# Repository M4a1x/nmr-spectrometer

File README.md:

<div align="center">
  
</div>

<div align="center">Building a 25MHz NMR spectrometer<br \>01.04.2023 - 30.09.2023</div>

<div align="center">

</div>

---

<div align="center"> magnETHical is a simple low-cost low-field 0.6T NMR spectrometer based on a RedPitaya and custom hardware. This repository contains everything to build your own. This includes simulations, specifications, full hardware descriptions and CAD designs, Python control code and reproducible measurement results.
</div>

## 📝 Table of Contents
- [📝 Table of Contents](#-table-of-contents)
- [🧐 About ](#-about-)
- [🏁 Getting Started ](#-getting-started-)
  - [✅ Prerequisites](#-prerequisites)
  - [🔧 Hardware](#-hardware)
  - [🖥️ Software](#️-software)
- [⚙️ Running the tests ](#️-running-the-tests-)
- [🧪 Usage ](#-usage-)
- [⛏️ Built Using ](#️-built-using-)
- [✍️ Authors ](#️-authors-)
- [🎉 Acknowledgements ](#-acknowledgements-)

## 🧐 About 
Since the discovery of the Zeeman effect in 1896 and its first use for spectroscopy in the 1940s a lot of technological advancements enabled the capture of increasingly better spectrums and the development of increasingly advanced techniques. Unfortunately, this advancement isn't cheap. Modern NMR spectroscopes cost a fortune, limiting access to this technology to well-funded research institutes, keeping out institutes from the southern hemisphere and limiting its exposure.

magnETHical seeks to provide a low-cost low-field NMR system not only capable of relaxometry but also spectroscopy for a price about an order of magnitude lower than existing devices. It's an open-source well-documented system that can be fully assembled in-house and consists of flexible components that are easily and readily available. 90% of the current ~10k€ price tag is comprised of the magnet with room for at least halving the price in the foreseeable future.

This repository seeks to provide everything needed to order, assemble and operate your own magnETHical NMR spectrometer.

## 🏁 Getting Started 

### ✅ Prerequisites
Great care has been taken to only use widely available free and open-source software so that this project may be built by anyone without any software licensing fees.

Throughout this README and the linked READMEs below a basic familiarity with the used software is assumed. However, anyone with some time on their hands should be able to follow them without much trouble after a very basic introduction to these programs. If you have trouble understanding any of the instructions, please feel free to open an issue - it's likely an error in this documentation and not on your side.

### 🔧 Hardware
The hardware consists of five main parts
- the [magnet](),
- the [digital signal generation, reception and processing board](),
- the [analogue amplification board](),
- the [electrical shimming system]() and
- the [NMR probe]().

Each of these parts can be built, assembled and verified independently of each other. For instructions on building these sub-systems, see the respective READMEs linked in the list above.

With all parts built, the final system needs to be assembled according to the following schematic.

The final assembly then looks something like this

### 🖥️ Software
Having built the hardware above the [Python control software]() can be used to capture spectra. See the linked article for a detailed guide on how to set up the software. We recommend a dedicated computer setup to run the experiments.

## ⚙️ Running the tests 
The simplest test is running marcos test without/with water. measure coil ringing

Explain how to run the automated tests for this system.

## 🧪 Usage 
To record spectra...

How to use the software/hardware. Recomenndations on analysis (Jupyter...)
Add notes about how to use the system.

## ⛏️ Built Using 

- Hardware
  - [KiCAD](https://www.kicad.org/) - ECAD for PCB Design
  - [FreeCAD](https://www.freecad.org/) - MCAD for Enclosures
  - [OpenSCAD](https://openscad.org/) - Parametric CAD for the probe
  - [LTSpice](https://www.analog.com/en/design-center/design-tools-and-calculators/ltspice-simulator.html) - Simulation of electronic circuits
- Software
  - [MaRCoS](https://github.com/vnegnev/marcos_extras) - Low-level control software for the RedPitaya and FPGA
  - [NumPy](https://numpy.org/)/[SciPy](https://scipy.org/)/[Matplotlib](https://matplotlib.org/) - High-level control software and analysis
- Documentation
  - [LaTeX](https://www.latex-project.org/) - Advanced typesetting system
  - [Sphinx](https://www.sphinx-doc.org) - Beautiful documentation

## ✍️ Authors 
- [Maximilian Stabel](mailto:mstabel@student.ethz.ch) - Idea & Initial work including Hardware & Software

## 🎉 Acknowledgements 
- Supervisor
  - [**Takuya Segawa**](https://chab.ethz.ch/forschung/institute-und-laboratorien/LPC/personen/people-details.html?persid=120573) for his supervision and encouragement
- Professors
  - [**Roland Riek**](https://chab.ethz.ch/en/the-department/people/faculty/person-detail.rriek.html) for giving me this opportunity
  - [**Sebastian Kozerke**](https://biomed.ee.ethz.ch/institute/People/person-detail.html?persid=61641) for taking me in as his Master's student
- Support
  - [**Alexander Däpp**](https://ssnmr.ethz.ch/the-group/people/person-detail.html?persid=147372) for his support and patience with the RF hardware
  - [**Tiago Ferreira das Neves**](https://chab.ethz.ch/en/the-department/people/a-z/person-detail.MjU3NzM4.TGlzdC82MDEsLTIxMzAxOTI4MDM=.html) for his electronics support

<div align="center">
  
</div>

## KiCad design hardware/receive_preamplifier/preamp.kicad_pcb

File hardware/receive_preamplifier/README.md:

# RX LNA Preamp

This folder contains the first amplifier in the RX chain, based on the [design of Martinos RF Lab](https://rflab.martinos.org/index.php?title=Low-noise_RF_Preamplifier) with the [PHA-13LN+](https://www.minicircuits.com/pdfs/PHA-13LN+.pdf) chip from mini-circuits.

This design could easily be adapted to be included in an all-in-one board including an RX preamplifier, RX amplifier, TX amplifier, TX power amplifier and TX/RX switch.

The design was adapted using the newest KiCAD version (7.0.2, 12.05.2023).

## Specifications
The receive amplifier needs to amplify the signal from uW level (~-30dbm, [Louis-Joesph and Lesot (2022)](../../literature/related_projects/foss_nmr_spectrometer_15MHz.pdf)) to around -2dbm (~0.5V @ 50Ohm) for the 16-bit ADC of the RedPitaya. Thus a gain of at least 28dB is needed. Previous work (see below) uses either a two or even three-stage design.

Furthermore, the design should be simple and easily reproducible. At best, it should be hand-solderable, without the need for a reflow oven or hot air gun. The parts should be easy to obtain and a low part count would be desirable as well. The target/carrier frequency is at 25MHz corresponding to the 1H Larmor frequency of the 0.6T magnet we're using.

One option would be to use an amplifier chain similar to [Martinos (MIT) lab](https://rflab.martinos.org/index.php?title=Main_Page) used in their MRI experiments for the reception. This consists of three stages, two PHA-13LN+ (~20€/eval board ~140€) and one ZFL-500LN+ (~125€). Sometimes the RX LNAs are already integrated into the T/R Switch - e.g. the [T/R Switch from Menküc](https://github.com/menkueclab/TR-Switch) uses the two PHA-13LN+ LNAs based on the design from Martinos lab. Since the maximum output level of the PHA-13LN+ is sufficiently high three PHA-LN13+ could be used as well.
> **TODO**
> Experimentally verify that 40dB (vs the 30dB estimate) are suitable for us, or if we need more/less amplification.

## Previous Work/Inspirations
- [Martinos Lab](https://rflab.martinos.org/index.php?title=Low-noise_RF_Preamplifier) uses a 3-stage design for their low-noise RF preamplifier. It consists of two PHA-13LN+ (Gain: 24dB, P1dB: 23dBm, Noise: 0.9dB @20MHz/5V) and one ZFL-500LN+ (Gain: 28dB, P1dB: 8dBm, Noise: 2.9dB, @5MHZ/15V) at the end before going into the measurement equipment. The two PHA-13LN+ are protected by BAV99 signal switching diodes (Vf=~0.7V), clamping the power at ~7dBm (PHA-13LN+ max. input pulse: 21dBm)
- The [tabletop MRI by Martinos Lab](https://tabletop.martinos.org/index.php?title=Hardware:RF) uses a 2-stage amplifier based on the [Gali-74+](https://www.minicircuits.com/pdfs/GALI-74+.pdf) (~4€/eval board 160€). (25dB gain, P1dB 19dbm, 2.7dB noise). Which is cheaper with comparable gain, but a higher noise figure. The RF-Switch uses [BYS-10](https://www.vishay.com/docs/86013/bys10.pdf) Schottky diodes with a V_f of 0.5V (-2dBm) for protection.
- [Hibino](https://www.sciencedirect.com/science/article/pii/S1090780718301745#b0110) used a CA-251F4 preamplifier (DC-10MHz, voltage 40dB gain, output power +-10mA max) which is unsuitable for our frequencies. They also used an AD603 variable preamplifier as their third 30dB variable gain input stage.
- The ZFL-500LN+ from mini-circuits has a gain of almost exactly 28dB when powered with at least 15V, with a P1dB of 8dBm over its whole specified range. Its noise figure is typically 2.9 dB.
- The [EasySDR](https://github.com/IgrikXD/Easy-SDR) uses a [PSA4-5043+]() or a [PGA-103+]() protected by BAV99 as well for their LNA. Optionally with a FV1206 or GE0805C-3 high-pass filter.

## Filters
- The [T/R-Switch by Menküc](https://github.com/menkueclab/TR-Switch) uses a low-pass filter at the output of the LNA chain, in our case this could be e.g. [SCLF-30+](https://www.mouser.ch/datasheet/2/1030/SCLF_30_2b-1701154.pdf) (~19€), [SCLF-27+](https://www.mouser.ch/datasheet/2/1030/SCLF_27_2b-1701261.pdf) (~13€/eval board 120€), or a custom design bessel/butterworth/... Should be a lowpass, since all other possibly interesting atoms have a lower resonant frequency than a single 1H.

## TODOs
- [ ] Experimentally verify the PHA-13LN+ boards I made
- [ ] Experimentally verify if a filter is needed/useful
- [ ] Design my own filter (cheaper!)
- [ ] Based on the above results make a filter (breakout) board
- [ ] Integrate together with own T/R Switch and TX amplifiers on one board

## Conclusions
1. Buy 1x PHA-13LN+ evaluation board
2. Buy 1x SCLF-27+ evaluation board
3. Build 3x PHA-13LN+ individual gain blocks based on Martinos Lab Design
4. Build 2x protection diode blocks with a BAV99 dual-diode each for the evaluation boards
5. Build 1x protection diode blocks with BYS-10 Schottky diodes for the RedPitaya inputs

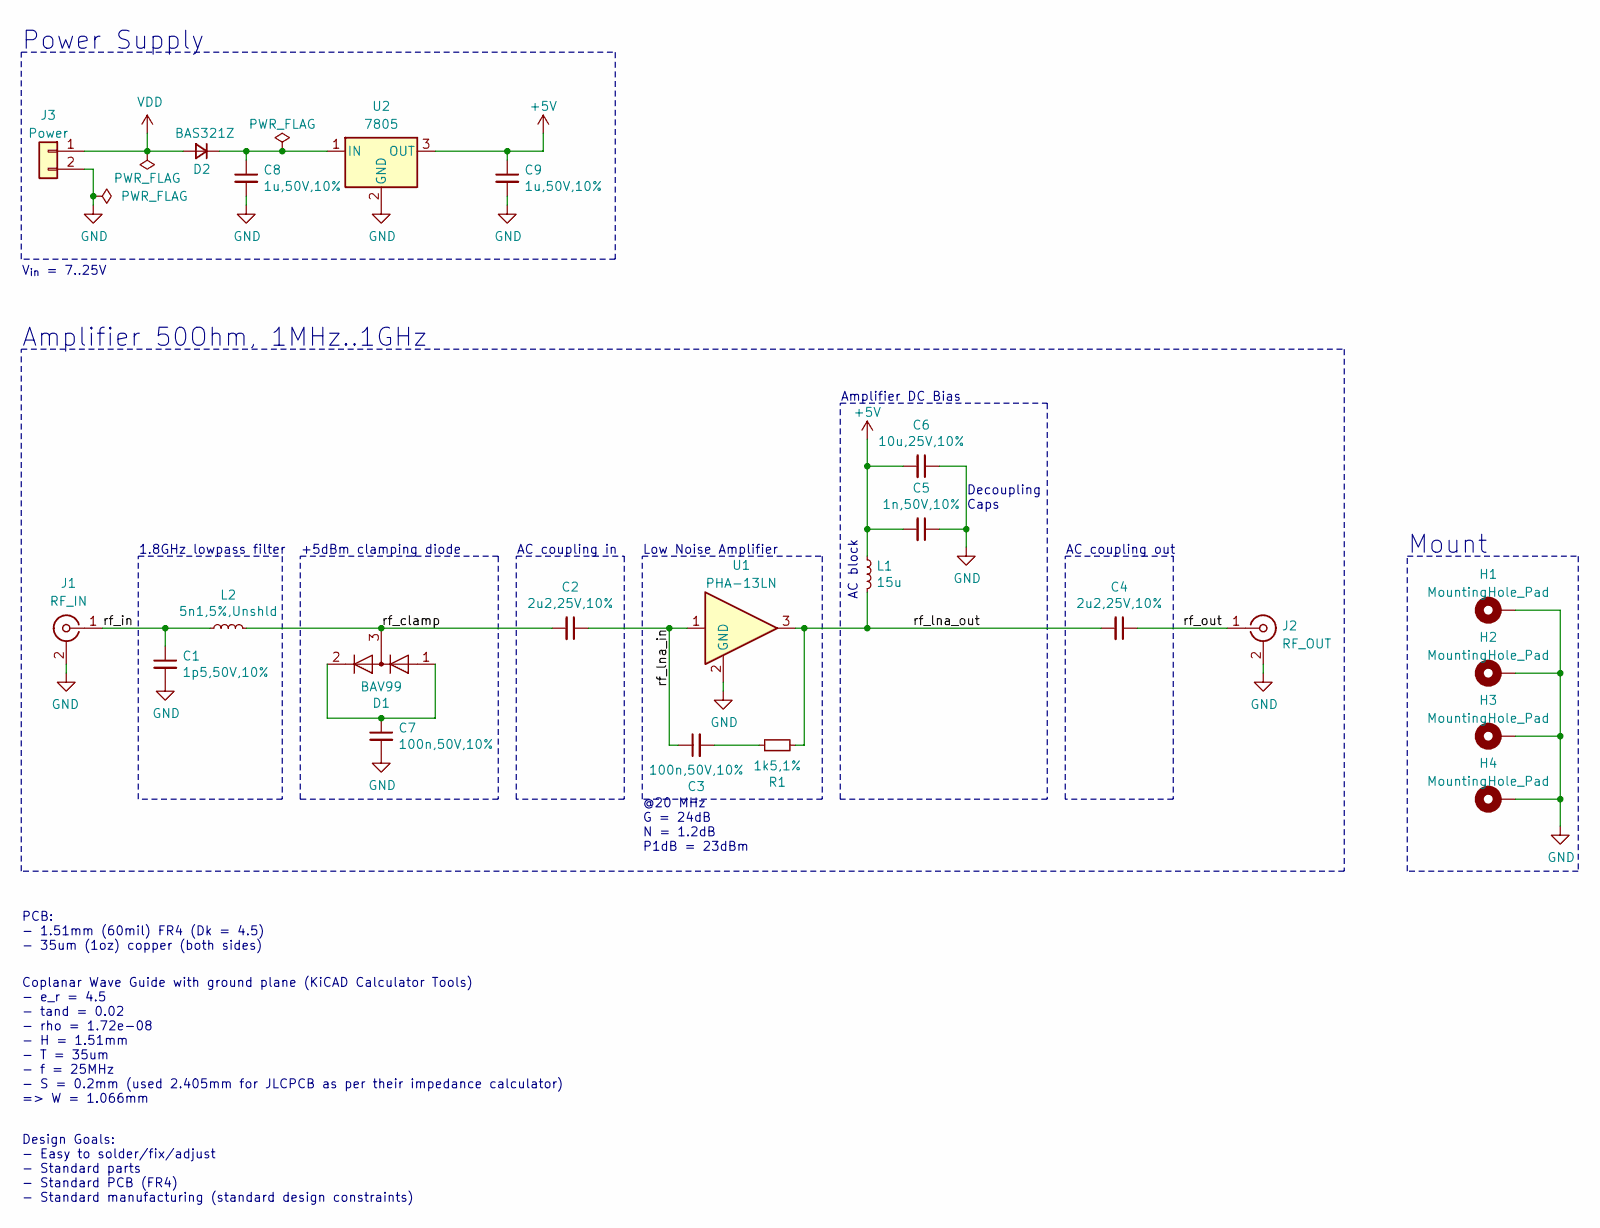
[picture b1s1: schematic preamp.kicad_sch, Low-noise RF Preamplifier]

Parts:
C1: 1p5,50V,10%; C_0805_2012Metric; MPN CC0805BRNPO9BN1R5; Mouser 603-CC805BRNPO9BN1R5
C2, C4: 2u2,25V,10%; C_0805_2012Metric; MPN CL21A225KAFNNNG; Mouser 187-CL21A225KAFNNNG
C3: 100n,50V,10%; C_0402_1005Metric_Pad0.74x0.62mm_HandSolder; MPN GRM155R71H104KE14D; Mouser 81-GRM155R71H104KE4D
C5: 1n,50V,10%; C_0805_2012Metric; MPN CL21B102KBANFNC; Mouser 187-CL21B102KBANFNC
C6: 10u,25V,10%; C_0805_2012Metric; MPN CL21A106KAYNNNG; Mouser 187-CL21A106KAYNNNG
C7: 100n,50V,10%; C_0805_2012Metric; MPN CL21B104KBCNNNC; Mouser 187-CL21B104KBCNNNC
C8, C9: 1u,50V,10%; C_0805_2012Metric; MPN CL21B105KBFNNNG; Mouser 187-CL21B105KBFNNNG
D1: BAV99; SOT-23; MPN BAV99; Mouser 583-BAV99
D2: BAS321Z; D_SOD-323_HandSoldering; MPN BAS321Z; Mouser 771-BAS321Z
H1, H2, H3, H4: MountingHole_Pad; MountingHole_2.2mm_M2_Pad_Via
J1: RF_IN; SMA_Molex_73251-1153_EdgeMount_Horizontal; MPN 142-0701-851; Mouser 530-142-0701-851
J2: RF_OUT; SMA_Molex_73251-1153_EdgeMount_Horizontal; MPN 142-0701-851; Mouser 530-142-0701-851
J3: Power; PinHeader_1x02_P2.54mm_Vertical; MPN 68491-102HLF; Mouser 649-68491-102HLF
L1: 15u; L_0805_2012Metric; MPN CV201210-150K; Mouser 652-CV201210-150K
L2: 5n1,5%,Unshld; L_0805_2012Metric; MPN 0805HT-5N1TJLC; Mouser 994-0805HT-5N1TJLC
R1: 1k5,1%; R_0402_1005Metric_Pad0.72x0.64mm_HandSolder; MPN RC0402FR-071K5L; Mouser 603-RC0402FR-071K5L
U1: PHA-13LN; SOT-89-3_Handsoldering; MPN PHA-13LN+; Mouser 139-PHA-13LN
U2: 7805; SOT-223-3_TabPin2; MPN UA78M05IDCYR; Mouser 595-UA78M05IDCYR

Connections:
+5V: C5.2, C6.2, C9.1, L1.1, U2.3 (OUT)
/rf_clamp: C2.2, D1.3 (K), L2.2
/rf_in: C1.1, J1.1 (In), L2.1
/rf_lna_in: C2.1, C3.1, U1.1
/rf_lna_out: C4.2, L1.2, R1.2, U1.3
/rf_out: C4.1, J2.1 (In)
GND: C1.2, C5.1, C6.1, C7.2, C8.2, C9.2, H1.1, H2.1, H3.1, H4.1, J1.2 (Ext), J2.2 (Ext), J3.2, U1.2 (GND), U2.2 (GND)
unnamed: C3.2, R1.1
unnamed: C7.1, D1.1 (K), D1.2 (A)
unnamed: C8.1, D2.1 (K), U2.1 (IN)
VDD: D2.2 (A), J3.1

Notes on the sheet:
Design Goals: - Easy to solder/fix/adjust - Standard parts - Standard PCB (FR4) - Standard manufacturing (standard design constraints)
Amplifier 50Ohm, 1MHz..1GHz
Amplifier DC Bias
V_{in} = 7..25V
+5dBm clamping diode
@20 MHz G = 24dB N = 1.2dB P1dB = 23dBm
AC block
AC coupling in
Low Noise Amplifier
Decoupling Caps
Power Supply
AC coupling out
1.8GHz lowpass filter
Mount
PCB: - 1.51mm (60mil) FR4 (Dk = 4.5) - 35um (1oz) copper (both sides)
Coplanar Wave Guide with ground plane (KiCAD Calculator Tools) - e_r = 4.5 - tand = 0.02 - rho = 1.72e-08 - H = 1.51mm - T = 35um - f = 25MHz - S = 0.2mm (used 2.405mm for JLCPCB as per their impedance calculator) => W = 1.066mm

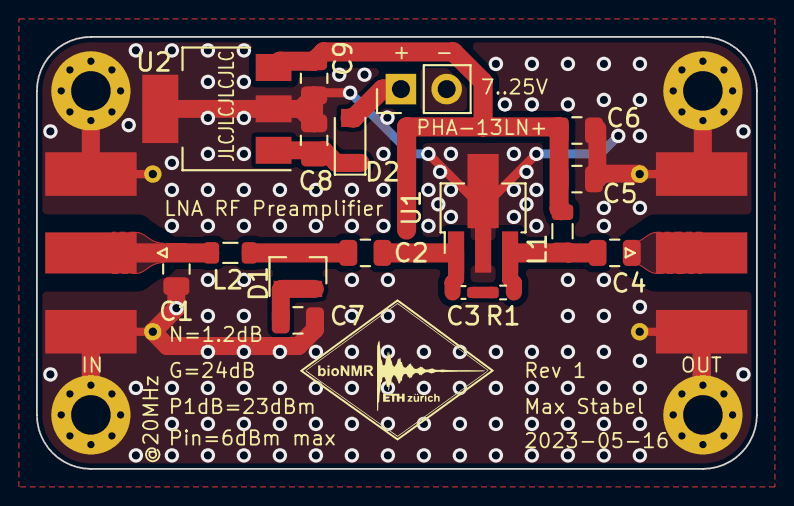
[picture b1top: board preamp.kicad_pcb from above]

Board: 2 copper layers, 40.0 x 24.0 mm, 23 parts (0 on the bottom side), 11 nets.

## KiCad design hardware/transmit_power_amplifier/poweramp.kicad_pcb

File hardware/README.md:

# Workspace

Here lies any code/digital work created during the project. This includes design files, measurement data, photographs and more. This is the main folder to be worked in.

| Folder                                                      | Description                                                                                                         |
| ----------------------------------------------------------- | ------------------------------------------------------------------------------------------------------------------- |
| [`nmr_probe`](./nmr_probe/)                                 | Probe and Probe construction                                                                                        |
| [`marcos`](./marcos/)                                       | MaRCoS software and control of the spectrometer                                                                     |
| [`32-channel_current_source`](./32-channel_current_source/) | Digitally controllable current source for driving the shims                                                         |
| [`tr_switch`](./tr_switch/)                                 | Transmit/Receive Switch for Switching between High-Power RF impulse transmission and low level FID signal reception |
| [`rx_lna_preamp`](./rx_lna_preamp/)                         | Low-Noise Amplifier for the amplification of the FID signal for the RedPitaya                                       |
| [`tx_power_amp`](./tx_power_amp/)                           | Power Amplifier to amplify the excitation pulse of the RedPitaya                                                    |

## General Setup
```text
+------------+                                            +--------------+
|            |     |\            |\                       | RX/TX Switch |
|            |     | \           | \                      |              |
|         TX |-----|  +----------|  +---------------------|---x  \       |         \ | /
|            |     | /           | /                      |       \      |          \|/
|            |     |/            |/                       |        \     |           |
|            |  ZFL-1000+      ZHL-3A+                    |         \    |           |
| Red Pitaya |                                            |          +---|-----------+
|            |                                            |              |
|            |       /|            /|           /|        |              |
|            |      / |           / |          / |        |              |
|         RX |-----+  |----------+  |---------+  |--------|---x          |
|            |      \ |           \ |          \ |        |              |
|            |       \|            \|           \|        |              |
|            |   ZFL-500LN+     PHA-13LN+   PHA-13LN+     |              |
+------------+                                            +--------------+
```

## Previous NMR Work

- Designing and building a low-cost portable FT-NMR spectrometer in 2019: A modern challenge (Alain Lous-Joseph, Philippe Lesot)
- OpenCore NMR (Kazuyuki Takeda)
- LabTools NMR spectrometer based on RedPitaya
- Pavel Demin's NMR spectrometer
- [Simple Low-Cost Tabletop NMR for chemical-shift-resolution spectra measurements](https://www.sciencedirect.com/science/article/pii/S1090780718301745#b0110). Home-built magnet, 60Hz resolution at 2.45MHz (58.8mT), in a later paper down to 1ppm.

## NMR Spectrometer Target Specifications

In addition to the [thesis description/project proposal](../literature/project_proposal/Master_Thesis_Proposal.pdf) we tried to meet the following specifications. This includes design requirements for the physical setup partially repeated in the various sub-sections in the `workspace` directory. Hardware should be reusable. The end goal would be of type "Bring your own Magnet", i.e. a Red Pitaya SDRLab 122.88, our board and magnet should be enough to do spectroscopy, when building their own probes.

- Larmor Frequency: 25MHz (0.6T)
- RF-field strength: x.xx mT
- pi/2 pulse length: x.xx us

> **TODO**
> Write down NMR target specifications here

In the end, separate modules should be developed for ease of reconfiguration. A nice addition would be a single board, including RX/TX amplifiers, switch and filters on one standard [Eurocard 3U (100mm x 160mm x 1.6mm)](https://en.wikipedia.org/wiki/Eurocard_(printed_circuit_board)) FR4 board, so it can be rack mounted, possibly with the common [DIN 41612](https://en.wikipedia.org/wiki/DIN_41612) (~~STEbus~~, VMEbus) connector at the back end. See also the [ARTIQ/Sinara project](https://github.com/sinara-hw/SiLPA_HL/issues/1).

## Red Pitaya SDRlab 122-16 (STEMlab 122-16)
The ADC of the RedPitaya is specified for an RF input voltage of 0.5Vpp. Its absolute maximum rating is 30VDC and 1Vpp RF (~4dBm). This has been verified by looking at the [used ADC](https://www.analog.com/media/en/technical-documentation/data-sheets/218543f.pdf) and the [RedPitaya Schematic](../../literature/instruments/Customer_Schematics_STEM122-16SDR_V1r1(Series1).PDF). Thus the input has to be protected from the power of the transmit cycle.

The easiest way to do this is to use a TVS diode for clamping the input to safe levels. Unfortunately, this severely degrades the ADCs performance according to [this Analog Devices Application Note](../../literature/instruments/rf-samp-adc-input-protection.pdf). The same AN suggests using [RB851Y](https://www.mouser.com/datasheet/2/348/rb851y-209815.pdf) Schottky diodes for ADC input protection
### Basic Specs
|                    |                           |
| ------------------ | ------------------------- |
| Processor          | DUAL CORE ARM CORTEX A9   |
| FPGA               | FPGA Xilinx Zynq 7020 SOC |
| RAM                | 512 MB (4 Gb)             |
| System Memory      | Micro SD up to 32 GB      |
| Console Connection | Micro USB                 |
| Power Connector    | Micro USB                 |
| Power Consumption  | 5 V, 2 A max              |

### RF Inputs
|                                   |                                       |
| --------------------------------- | ------------------------------------- |
| RF input channels                 | 2                                     |
| Sample rate                       | 122.88 MS/s                           |
| ADC resolution                    | 16 bit                                |
| Input impedance                   | 50 Ohm                                |
| Full scale voltage range          | 0.5 Vpp/-2 dBm                        |
| Input coupling                    | AC                                    |
| Absolute max. Input voltage range | DC max 50 V (AC-coupled) 1 Vpp for RF |
| Input ESD protection              | Yes                                   |
| Overload protection               | DC voltage protection                 |
| Bandwidth                         | 300 kHz - 550 MHz                     |

### RF Outputs
|                         |                                  |
| ----------------------- | -------------------------------- |
| RF output channels      | 2                                |
| Sample rate             | 122.88 MS/s                      |
| DAC resolution          | 14 bit                           |
| Load impedance          | 50 Ohm                           |
| Voltage range           | 0.5 Vpp/ -2 dBm (50 Ohm load)    |
| Short circut protection | N/A, RF transformer & AC-coupled |
| Connector type          | SMA                              |
| Output slew rate        | N/A                              |
| Bandwidth               | 300 kHz - 60 MHz                 |

Next Steps:
1. Build 2x Protection diode blocks with 2x BYS-10 schottky diodes each for input protection (limit power to 4dBm/+-0.5V/1Vpp)

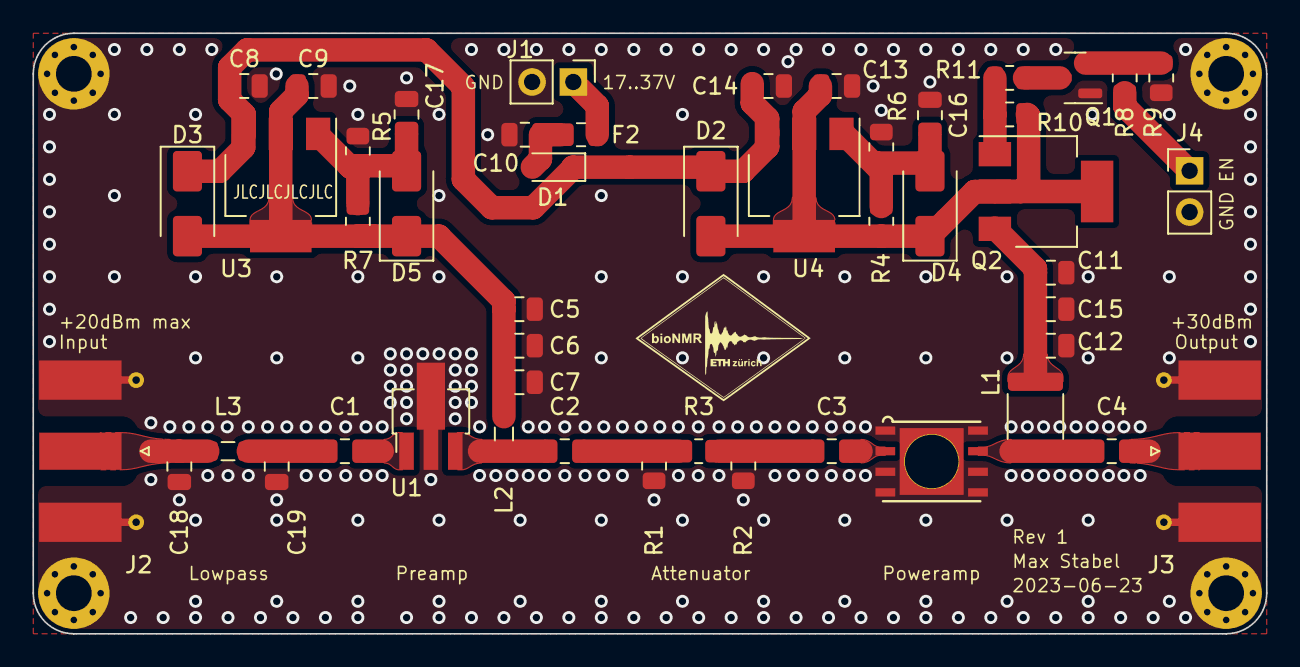
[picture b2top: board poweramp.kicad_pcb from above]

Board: 2 copper layers, 76.0 x 37.0 mm, 53 parts (0 on the bottom side), 22 nets.

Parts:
C1, C2, C3, C4, C10, C15: 100n/50V; C_0805_2012Metric
C5, C11: 1u/50V; C_0805_2012Metric
C6, C12: 1n/50V; C_0805_2012Metric
C7: 68p/50V; C_0805_2012Metric
C8, C9, C13, C14: 1u,50V,10%; C_0805_2012Metric
C16, C17: 10u,50V,10%; C_0805_2012Metric
C18, C19: 130p/50V; C_0805_2012Metric
D1: SS13HE; D_SOD-323_HandSoldering
D2, D3, D4, D5: S1B (1N4002); D_SMA
F2: Polyfuse; Fuse_0805_2012Metric
H1, H2, H3, H4: MountingHole_Pad; MountingHole_2.2mm_M2_Pad_Via
J1: Power; PinHeader_1x02_P2.54mm_Vertical
J2: RF_IN; SMA_Molex_73251-1153_EdgeMount_Horizontal
J3: RF_OUT; SMA_Molex_73251-1153_EdgeMount_Horizontal
J4: Power_Enable; PinHeader_1x02_P2.54mm_Vertical
L1: 5u6; L_1812_4532Metric
L2: 470n; L_0805_2012Metric
L3: 360n; L_0805_2012Metric
Q1: MMBT3904; SOT-23
Q2: BCP51; SOT-223-3_TabPin2
R1, R2: 150; R_0805_2012Metric
R3: 37R4; R_0805_2012Metric
R4, R7: 240, 1%; R_0805_2012Metric
R5: 715, 1%; R_0805_2012Metric
R6: 2k43, 1%; R_0805_2012Metric
R8, R10: 1k; R_0805_2012Metric
R9: 10k; R_0805_2012Metric
R11: 4k7; R_0805_2012Metric
U1: ADL5536; SOT-89-3_Handsoldering
U2: PHA-202+; DL1636_HandSolder
U3, U4: LM317_SOT-223; SOT-223-3_TabPin2

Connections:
+5V: C5.1, C6.1, C7.1, C9.1, D3.2 (A), D5.1 (K), L2.1, R7.1, U3.2 (VO)
+14V: C13.1, D2.2 (A), D4.1 (K), Q2.2 (C), R4.1, R11.2, U4.2 (VO)
/amp_in: C3.2, U2.2
/amp_out: C4.1, L1.2, U2.7
/att_in: C2.2, R1.1, R3.1
/att_out: C3.1, R2.1, R3.2
/filter_out: C1.1, C19.2, L3.2
/preamp_in: C1.2, U1.1
/preamp_out: C2.1, L2.2, U1.3
/rf_in: C18.2, J2.1 (In), L3.1
/rf_out: C4.2, J3.1 (In)
GND: C5.2, C6.2, C7.2, C8.2, C9.2, C10.1, C11.2, C12.2, C13.2, C14.2, C15.2, C16.2, C17.2, C18.1, C19.1, H1.1, H2.1, H3.1, H4.1, J1.2, J2.2 (Ext), J3.2 (Ext), J4.2, Q1.1 (E), R1.2, R2.2, R5.2, R6.2, R9.1, U1.2 (GND), U2.1 (EP), U2.3 (EP), U2.4 (EP), U2.5 (EP), U2.6 (EP), U2.8 (EP), U2.EP (GND)
unnamed: C10.2, D1.2 (A), F2.2
unnamed: C16.1, D4.2 (A), R4.2, R6.1, U4.1 (ADJ)
unnamed: C17.1, D5.2 (A), R5.1, R7.2, U3.1 (ADJ)
unnamed: F2.1, J1.1
unnamed: J4.1, R8.1
unnamed: Q1.2 (B), R8.2, R9.2
unnamed: Q1.3 (C), R10.1
unnamed: Q2.1 (B), R10.2, R11.1
VCC: C8.1, C14.1, D1.1 (K), D2.1 (K), D3.1 (K), U3.3 (VI), U4.3 (VI)
VDD: C11.1, C12.1, C15.1, L1.1, Q2.3 (E)

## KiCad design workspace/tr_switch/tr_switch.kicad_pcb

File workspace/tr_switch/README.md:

# TX/RX Switch

The T/R Switch needs to handle  ~5W, max 10W in transmit power (Bruker max. 5W!). Two main options exist:
- passive T/R Switch (lambda/4 + passive diodes) as built by Alex. Possibly change the Diodes to Schottky diodes for smaller leak-through power. Why aren't we using PIN diodes?
- active T/R switch (lambda/4 + pin diode)
  - built from discrete components (e.g. [this Github by Menküc](https://github.com/menkueclab/TR-Switch), explained in  [this Infineon AN](https://www.infineon.com/dgdl/Infineon-AN_1809_PL32_1810_172154_PIN%20diodes%20in%20RF%20sw%20applications-AN-v01_00-EN.pdf?fileId=5546d46265f064ff016643e2bc241042)) or the [OCRA T/R Switch](https://zeugmatographix.org/ocra/2021/09/30/transmit-receive-switch-for-the-ocra-tabletop-mri-system/) (PIN Diodes ~2CHF)
  - commercial chip (e.g. [M3SWA-2-50DR up to 20dBm](https://www.minicircuits.com/pdfs/M3SWA-2-50DR.pdf) used by OpenCoreNMR for pulse modulation/[PE42520](https://www.psemi.com/pdf/datasheets/pe42520ds.pdf) (5W)/[QPC6324](https://www.mouser.ch/datasheet/2/412/QPC6324_Data_Sheet-1265756.pdf) (5W)/[HMC544A (reflective)](https://www.analog.com/media/en/technical-documentation/data-sheets/hmc544ae.pdf) (5W) used in Sinara Booster/[MASW-000932](https://www.mouser.ch/datasheet/2/249/MASW_000932-838129.pdf) (max 80W) see [DigiKeys Antenna Switching Note](https://www.digikey.ch/en/articles/how-to-quickly-safely-switch-antenna-transducer-transmit-receive-modes) or [Digikeys RF Switch Note](https://www.digikey.de/de/articles/choosing-an-rf-switch)) ~5CHF-10CHF
  - [20CHF Commercial RF Switch](https://www.mikroe.com/rf-switch-click) used in [SiLPA](https://github.com/sinara-hw/SiLPA_HL/issues/1)
  - [Mini circuits packaged SPDT active switch ZX80-DR230-S](https://www.mouser.de/ProductDetail/Mini-Circuits/ZX80-DR230-S+?qs=A6eO%252BMLsxmSxGVKhwBQ6Xg%3D%3D&_gl=1*166vu6r*_ga*dW5kZWZpbmVk*_ga_15W4STQT4T*dW5kZWZpbmVk*_ga_1KQLCYKRX3*dW5kZWZpbmVk)
  
For simplicity of use, a passive switch would be advantageous if possible. The passive solution should leak only a little power that can be clamped by the protection diodes before the amplifier. This has the advantage that we can see the ringing of the coil and accurately start measuring after it ringed down?

Next steps:
1. For now Alex' amplifier can be used the 6dBm output power that leaks from input to output can be clamped at every stage of the amplifier chain.
2. Since we don't have that much power the design could probably be made smaller, e.g. only one lambda/4 filter instead of three
3. Use Schottky Diodes instead of normal signal switching diodes for a lower power leak
4. A switch

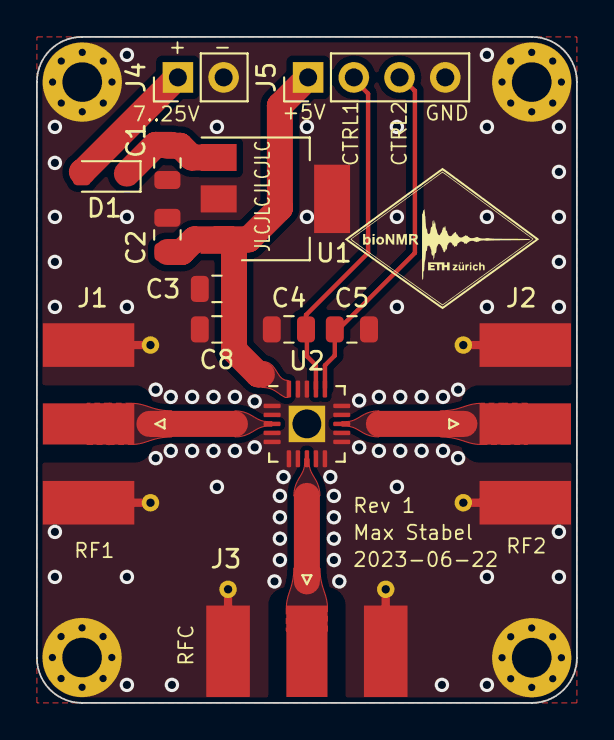
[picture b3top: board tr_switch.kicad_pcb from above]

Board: 2 copper layers, 30.0 x 37.0 mm, 18 parts (0 on the bottom side), 9 nets.

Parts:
C1, C2: 1u,50V,10%; C_0805_2012Metric
C3: 1u/50V; C_0805_2012Metric
C4, C5: 200p/50V; C_0805_2012Metric
C8: 100n/50V; C_0805_2012Metric
D1: BAS321Z; D_SOD-323_HandSoldering
H1, H2, H3, H4: MountingHole_Pad; MountingHole_2.2mm_M2_Pad_Via
J1: RF1; SMA_Molex_73251-1153_EdgeMount_Horizontal
J2: RF2; SMA_Molex_73251-1153_EdgeMount_Horizontal
J3: RFC; SMA_Molex_73251-1153_EdgeMount_Horizontal
J4: Power; PinHeader_1x02_P2.54mm_Vertical
J5: Control; PinHeader_1x04_P2.54mm_Vertical
U1: 7805; SOT-223-3_TabPin2
U2: QPC6324; QFN-20-1EP_4x4mm_P0.5mm_EP2x2mm_HandSolder

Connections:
+5V: C2.1, C3.1, C8.1, J5.1, U1.3 (OUT), U2.20
/VDD_p: C1.1, D1.1 (K), U1.1 (IN)
/rf1: J1.1 (In), U2.3
/rf2: J2.1 (In), U2.13
/rfc: J3.1 (In), U2.8
GND: C1.2, C2.2, C3.2, C4.1, C5.1, C8.2, H1.1, H2.1, H3.1, H4.1, J1.2 (Ext), J2.2 (Ext), J3.2 (Ext), J4.2, J5.4, U1.2 (GND), U2.1, U2.2 (GND), U2.4 (GND), U2.5 (GND), U2.6 (GND), U2.7 (GND), U2.9 (GND), U2.10 (GND), U2.11 (GND), U2.12 (GND), U2.14 (GND), U2.15 (GND), U2.18 (GND), U2.19 (GND), U2.21 (GND)
unnamed: C4.2, J5.2, U2.17
unnamed: C5.2, J5.3, U2.16
VDD: D1.2 (A), J4.1

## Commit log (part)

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2023-03-18 Add preliminary tooling
    This includes .gitignore, CI for github & gitlab, VS Code settings,
    extensions and Docker container configuration as well as a
    LuaLaTeX .latexmkrc file
2023-03-18 Add simple READMEs in the subfolders
2023-03-18 Add .gitlab-ci.yml
2023-03-18 Simplify .gitlab-ci.yml for testing
2023-03-18 Update .gitlab-ci.yml file
2023-03-18 Move workflow to correct folder
2023-03-18 Fix workflow working directory
2023-03-18 Remove gitlab CI
2023-03-18 Move extension settings from container to vscode settings.json
2023-04-03 Add gaussmeter documents
2023-04-03 Add magnet specifications
2023-04-03 Remove latex report configuration (for now)
2023-04-04 Add 3D Printing instructions
2023-04-04 Add Andrew McDowell's rf probe holder
2023-04-04 Add more complete map data for shimmed magnet
2023-04-04 Add Andrew McDowell's rf probe holder prusa project
2023-04-04 Add 230403-probe_holder_v1.scad incl. print files
2023-04-05 Auto format probe holder v1
2023-04-05 Add probe_holder_v1 printed gcode un MK3S printer
2023-04-05 Add GPLv3 License
2023-04-05 Add sequences python project
    This includes the my_first_experiment.py from the tutorial.
    The script has been modified to work with hatch in a separate python env
2023-04-06 Add probe holder images
2023-04-06 Add some more NMR literature
2023-04-06 Add readme to sequences project
2023-04-06 Make linter happy
2023-04-06 Fix first my_first_experiment.py
2023-04-06 Add Simulator startup to README
2023-04-06 Update readme with `make` instruction
2023-04-06 Add simulator output plot instructions
2023-04-06 Add RedPitaya configuration to README.md
2023-04-09 Use my branch of marcos_client
2023-04-12 Add LibreOffice locks to gitignore
2023-04-12 Add SD-Card backup command to README
2023-04-13 Add first kickoff presentation template
2023-04-13 Add first rf coil documentation
2023-04-14 Add ocra yocto image setup on red pitaya
2023-04-14 Verified probe rf-coil diameter
2023-04-14 Fix thesis deadline
2023-04-14 Add how to flash red pitaya base image
2023-04-14 Add some ETH colors
2023-04-14 Change colours of the theme
2023-04-17 Add presentation slides on the NMR spectrometer project
2023-04-17 Fix typo in filename
2023-04-17 Add Pavel Demin RedPitaya Fosdem 2016 talk
2023-04-18 Add the passive TX/RX rf switch documentation
2023-04-20 Add pictures to workspace
2023-04-20 Add some literature I found
2023-04-20 Add probe v1 vna tune and match captures
2023-04-20 Update probe v1 values
2023-04-20 Add RedPitaya datasheet
2023-04-20 Add VNA pictures of andrew's probe after tuning and matching
2023-04-20 Fix/add first experiment configuration
2023-04-20 Add termination explanation
2023-04-21 Add full power test
2023-04-21 Move sequences out of src folder
2023-04-28 Add RedPitaya specs
2023-04-28 Move current source to workspace
2023-04-28 Add meeting presentation
2023-04-28 Add osci/laptop captures to marcos readme
2023-05-02 Add reference to current source design options
2023-05-04 Add marcos test_server.py errors
2023-05-04 Start writing down target specs
2023-05-04 Add VNA manual
2023-05-06 Amplifier spec literature and thoughts
2023-05-22 Add RX LNA Preamp KiCAD design
2023-05-23 Order at JLCPCB with modified rf clearances
2023-05-24 WIP: split up readmes for amplifiers and switch
2023-05-30 Restructure LNA/PA/Switch READMEs
2023-05-31 Fix rx lna preamp production output settings
2023-05-31 Add RF/Circuits literature
2023-06-02 Add LNA board measurements
2023-06-07 RP protection clamping pictures
2023-06-08 Add RedPitaya input protection diodes simulations
2023-06-08 Fix input protection diode simulation library include
2023-06-14 Add commercial SPDT switch as option
2023-06-14 Add enable switch to poweramp
2023-06-14 Add theory literature
2023-06-14 Add various diodes to clamping_diodes simulation
2023-06-28 Add power supply channel ltspice simulation
2023-06-28 Add LTSpice/KiCAD gitignores
2023-06-28 Remove gerber outputs
2023-06-28 Get poweramp Rev 1 ready for ordering
2023-06-28 Move current source simulations in subfolder
2023-07-06 Add Thermometer Readme
2023-07-07 Add switch, diode and amp measurements
2023-07-10 Add some first measurements with andrews probe
2023-07-14 Add first FID signal measurements
2023-07-18 Add nicer matplotlib plots
2023-07-18 add nmrglue dependency
2023-07-19 Add convenience methods for reading/writing files
2023-07-19 Add simple automated fft to 1D FID class
2023-07-19 Update simple_experiment to plot with FID object
2023-07-19 Restructure python spectrometer control library
2023-07-19 Add andrew probe water FID measurement and scripts
2023-07-20 Include first water/coil measurements
2023-07-21 Upload plots of fid
2023-07-23 Add related projects (Hilty)
2023-07-23 Cleanup pulse.py
2023-07-23 Enable pytest in vscode settings.json
2023-07-25 Add spin echo pulse sequence
2023-07-26 Refactor pulse.py for simpler use and more understandable code
2023-07-27 Ass spin_echo and rabi_nutation experiments
2023-07-27 Add simple fit to FID
2023-07-27 Add some NMR analysis software ideas
2023-08-04 Move python spectrometer interface to own folder
2023-08-07 Add first final README draft
2023-08-07 Update control software dependencies
2023-08-08 Add jupyter interactive plot dependency
2023-08-08 Add demo jupyter notebook
2023-08-08 Bump minimum python version requirement to 3.10
2023-08-08 Format demo notebook
2023-08-08 Support multiple recordings per sequence
2023-08-09 Restructure repository
2023-08-09 WIP: Add spectrometer setup scripts. Still need debugging
2023-08-09 Center heading in gitlab as well
2023-08-09 Add prerequisites emoji
2023-08-09 Debug server setup automation
2023-08-10 Add kaobook documentation example for thesis
2023-08-10 Add dotfiles to report
2023-08-10 Move tex class/package files into subfolder
2023-08-10 Remove template notice
2023-08-10 Update kaobook to newest version
2023-08-10 Try and change font
2023-08-10 Patch fonts inside kao.sty
2023-08-10 Only compile report on report update
2023-08-10 Path kao.sty unitnumberfont
2023-08-10 Add ethesis.sty
2023-08-10 Add customized titlepage, colophon and dedication
2023-08-10 Update report preamble
2023-08-11 Remove CI integration
2023-08-11 Mention latexmkrc in the report readme
2023-08-11 Add note on marcos readme vs spectrometer
2023-08-11 Update logo
2023-08-12 Add simple CLI for managing the server
2023-08-12 Add more shields
2023-08-15 Cleanup report source
2023-08-15 Revert to standard kao class
2023-08-15 Move kao example text in subfolder
2023-08-15 Add circuitikz to tex package
2023-08-15 Combine results and discussion chapters
2023-08-15 Use IEEE citation style
2023-08-16 Add NMR publications jupyter notebook
2023-08-16 Finish first draft of introduction
2023-08-17 Change line width between countries of nmr citations world map
2023-08-17 Start separating record and process of data
2023-08-18 Update record_fid, process_fid and full_demo to new api
2023-08-18 Rename data "pulse_file" to "pulse"
2023-08-18 Use dots instead of lines for raw data
2023-08-18 Split record_spin_echo to record and process
2023-08-18 Add thesis format to plot.py
2023-08-18 Remove ETH colors from processing
2023-08-18 Add simple automatic zero order phase shift correction
2023-08-18 Remove unused imports
2023-08-18 Fix CLI commands
2023-08-18 Create t2_decay process notebook
2023-08-20 Update full_demo notebook and corresponding plotting functions
2023-08-20 Add single pulse experiment with probe_holder_v1 and water
2023-08-20 Remove processed data from repo
2023-08-20 Debug record_rabi_nutation and fid
2023-08-21 Use squre for lorentzian
2023-08-21 Adjust python notebook measurement scripts
2023-08-21 Add FWHM and T2* estimation to FID python notebook
2023-08-21 WIP: Rabi nutation 3D plot
2023-08-21 Improve rabi_nutation processing
2023-08-21 Fix unpacking bug in plot_simple_fft
2023-08-21 Format python code
2023-08-21 Edit rabi nutation record parameters
2023-08-21 Update fid sampling rate
2023-08-21 Update process_fid
2023-08-22 process_fid.py: Make separate plot for fit
2023-08-22 Add FID recording of water for thesis
2023-08-22 Process FID water andrew probe for thesis
2023-08-22 Adjust record_fid.py script for thesis
2023-08-22 Fix typo
2023-08-22 Add rabi nutation for thesis
2023-08-22 Use inline widgets for rabi nutation
2023-08-22 Add complete rabi nutation processing pdfs
2023-08-22 WIP: T2 decay
2023-08-23 Add spin echo data for thesis
2023-08-23 WIP: T2 decay process script
2023-08-23 Make lorentz a class
2023-08-23 WIP: Add Spectrum class
2023-08-25 Add first t2_decay_measurement
2023-08-25 Format code
2023-08-25 Format record scripts
2023-08-25 Format process scripts
2023-08-25 Update slicing on spectrum object
2023-08-25 Update spin echo processing to new interface
2023-08-25 Update rabi nutation to new interface
2023-08-25 Add all figures and data for thesis
2023-08-28 Add figures to report
2023-08-28 Add lambda to decay print
2023-08-28 Update spin echo figure in thesis
2023-08-28 Continue results
2023-08-28 Add simulated Toluene data
    Simulated at B_0 = 25MHz with a linewidth of 50Hz with MestReNova 14.3.3
2023-08-28 Crop toluene simulation data
2023-08-28 Add toluene recording and processing
2023-08-29 Adapt kaorefs and ethesis for minted and chemmacros
2023-08-30 Add defence presentation template
2023-08-30 add intro and results to defence
2023-08-31 Add chemical structures
2023-08-31 Continue discussion of results in thesis
2023-09-04 Add price slides and spin echo backup slides
2023-09-04 Update probe readme
2023-09-05 WIP defence presentation
2023-09-06 Record another toluene fid
2023-09-07 Add 3D render for 32-channel-current-source
2023-09-07 Add shimming error pdf examples
2023-09-07 Update toluene fid & fft
2023-09-07 Add 32-channel_current_supply to presentation
2023-09-08 Add simple nmrglue powered peak picking, fitting and spectrum simulation
2023-09-10 Update demo
2023-09-10 Add combined LNA/attenuator/filter/protection osci measurement
2023-09-10 Add test signal measurement with 50dB attenuator
    Resulting in a sine signal of -86dBm/31uV
2023-09-10 Add test signal with 56dB attenuator 25MHz signal
    Resulting in a signal amplitude of -92dBm/16uV
2023-09-10 Add static reveal.js
2023-09-10 Update fid processing fitting and format
2023-09-10 Add slides shortcut as hatch run command
2023-09-10 Add reveal.js distribution
2023-09-10 Remove unnecessary reveal.js
2023-09-10 Add testrun of full_demo
2023-09-11 Add SNR and amplitude estimations
2023-09-11 Add rabi nutation period marker line
2023-09-11 Presentation update
2023-09-12 Update python software roadmap
2023-09-12 Shorten presentation
2023-09-12 Update fitting
2023-09-12 Change equality to corespondance sign
2023-09-12 Adjust console slide image placement
2023-09-13 Add keeler nmr book
2023-09-13 Add images from presentation to report folder
2023-09-18 Add fourier transform graphs to concept
2023-09-18 Add block diagram including highlights
2023-09-19 WIP: Materials & Methods
2023-09-21 Methods chapter introduction
2023-09-22 Add schematics to appendix
2023-09-24 WIP: Results and Discussion
2023-09-24 Add thesis render to repo
2023-09-25 Remove duplicate static logo asset
2023-09-25 First draft of results
2023-09-25 Add SNR estimation to experimental results
2023-09-27 Update user guide and conclusion chapters
2023-09-27 Start on abstract
2023-09-27 Add the magnet
2023-09-28 Add TR switch chapter
2023-09-29 Add probe and software to thesis
2023-09-30 n't -> not substitution in thesis
2023-09-30 's -> is substitution in thesis
2023-09-30 Remove kao example chapters
2023-09-30 Add Takuya's suggestions into thesis
2023-09-30 Fix lna feedback loop
2023-09-30 Add low noise amplifier to thesis
2023-09-30 Add price table
2023-09-30 Edit current source simulation output to be more legible
2023-09-30 Add current source chapter to thesis
2023-09-30 Add protection diodes
2023-09-30 Thesis final version

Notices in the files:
README.md:
License: GPL-3.0
